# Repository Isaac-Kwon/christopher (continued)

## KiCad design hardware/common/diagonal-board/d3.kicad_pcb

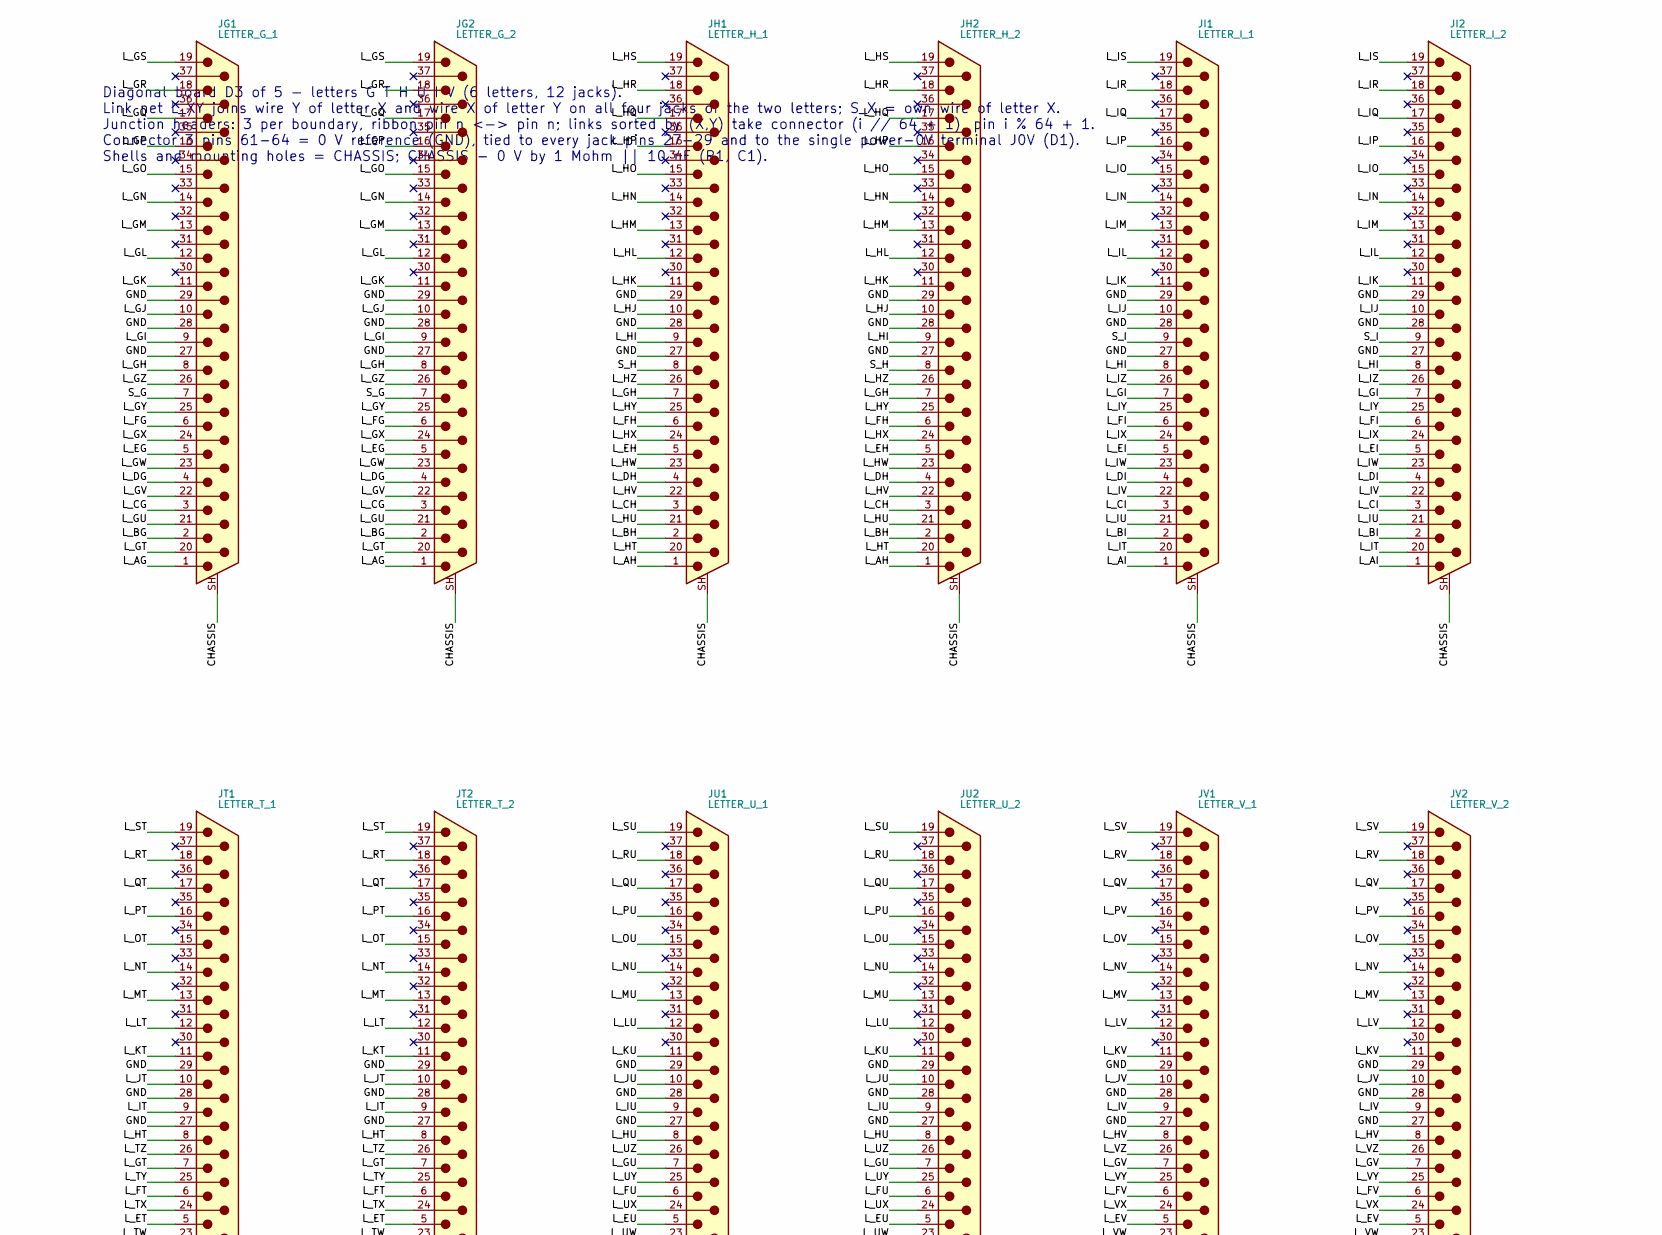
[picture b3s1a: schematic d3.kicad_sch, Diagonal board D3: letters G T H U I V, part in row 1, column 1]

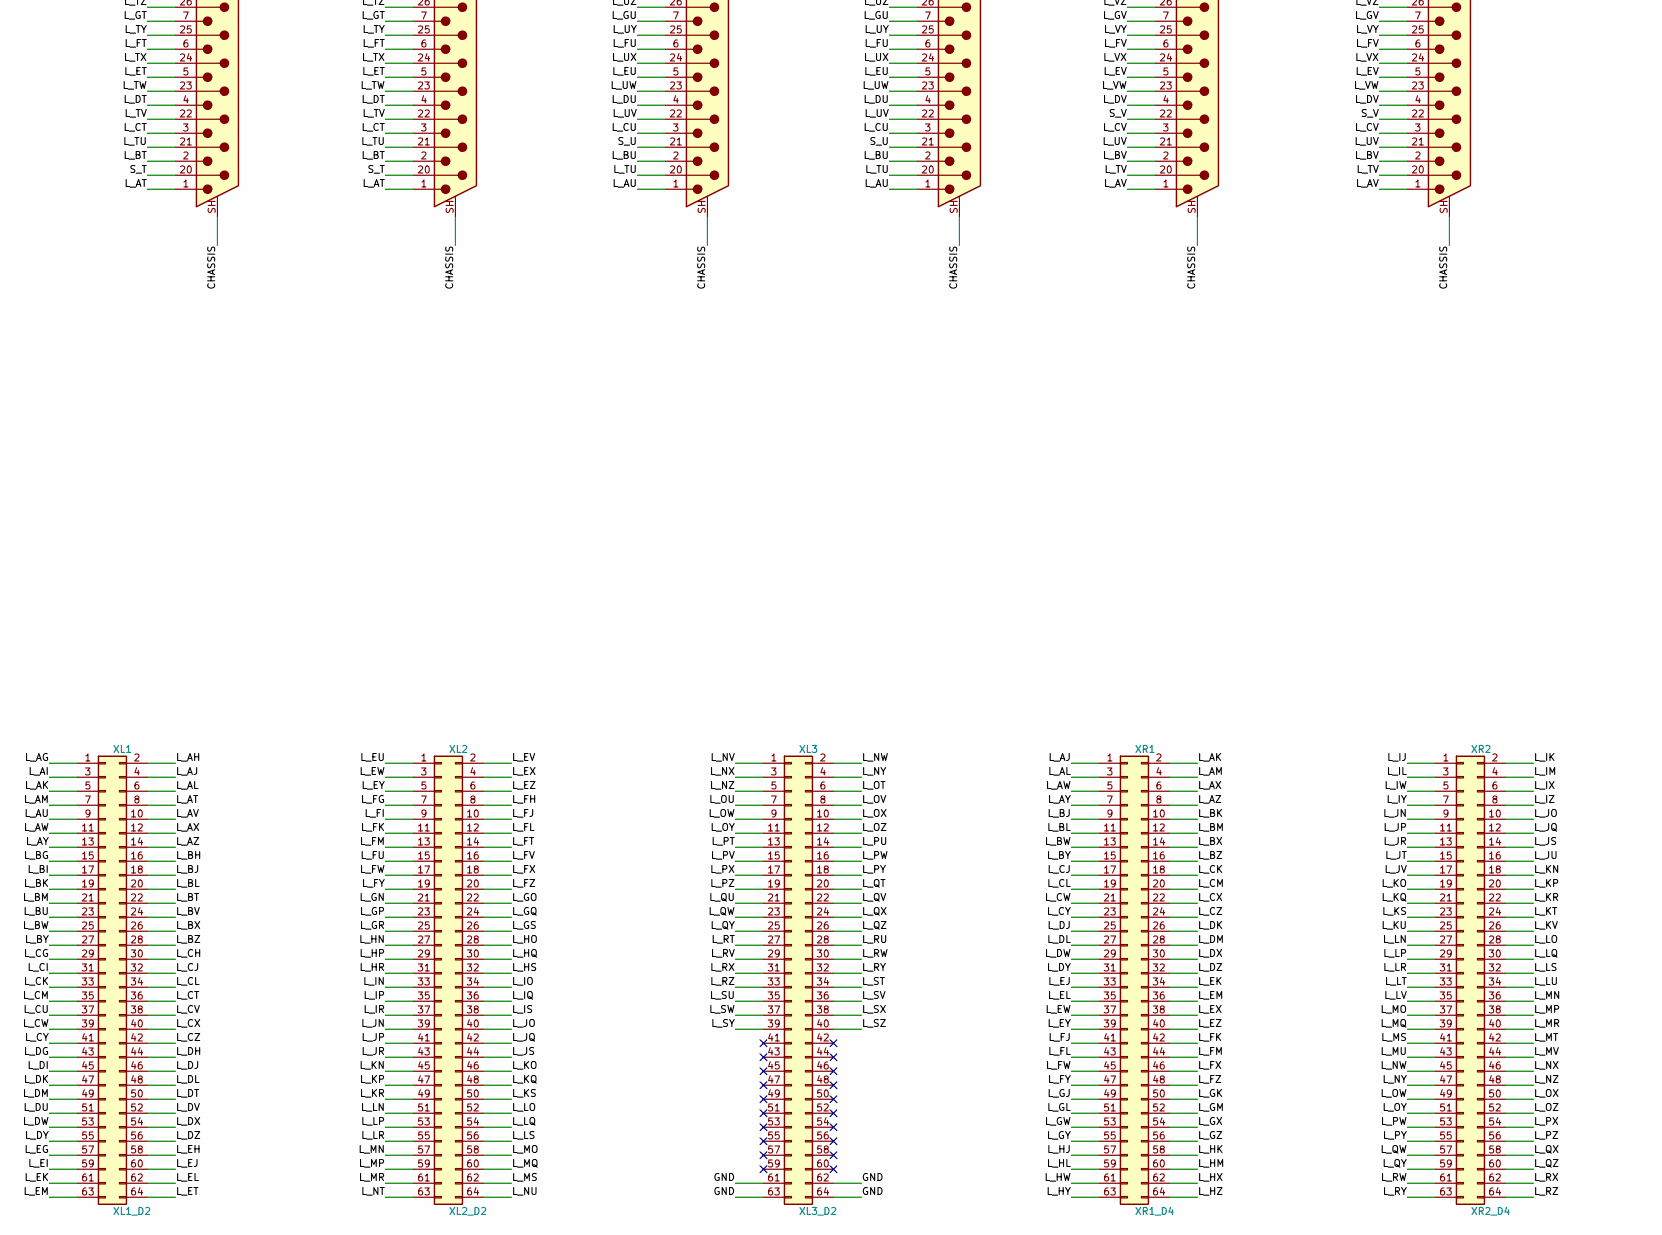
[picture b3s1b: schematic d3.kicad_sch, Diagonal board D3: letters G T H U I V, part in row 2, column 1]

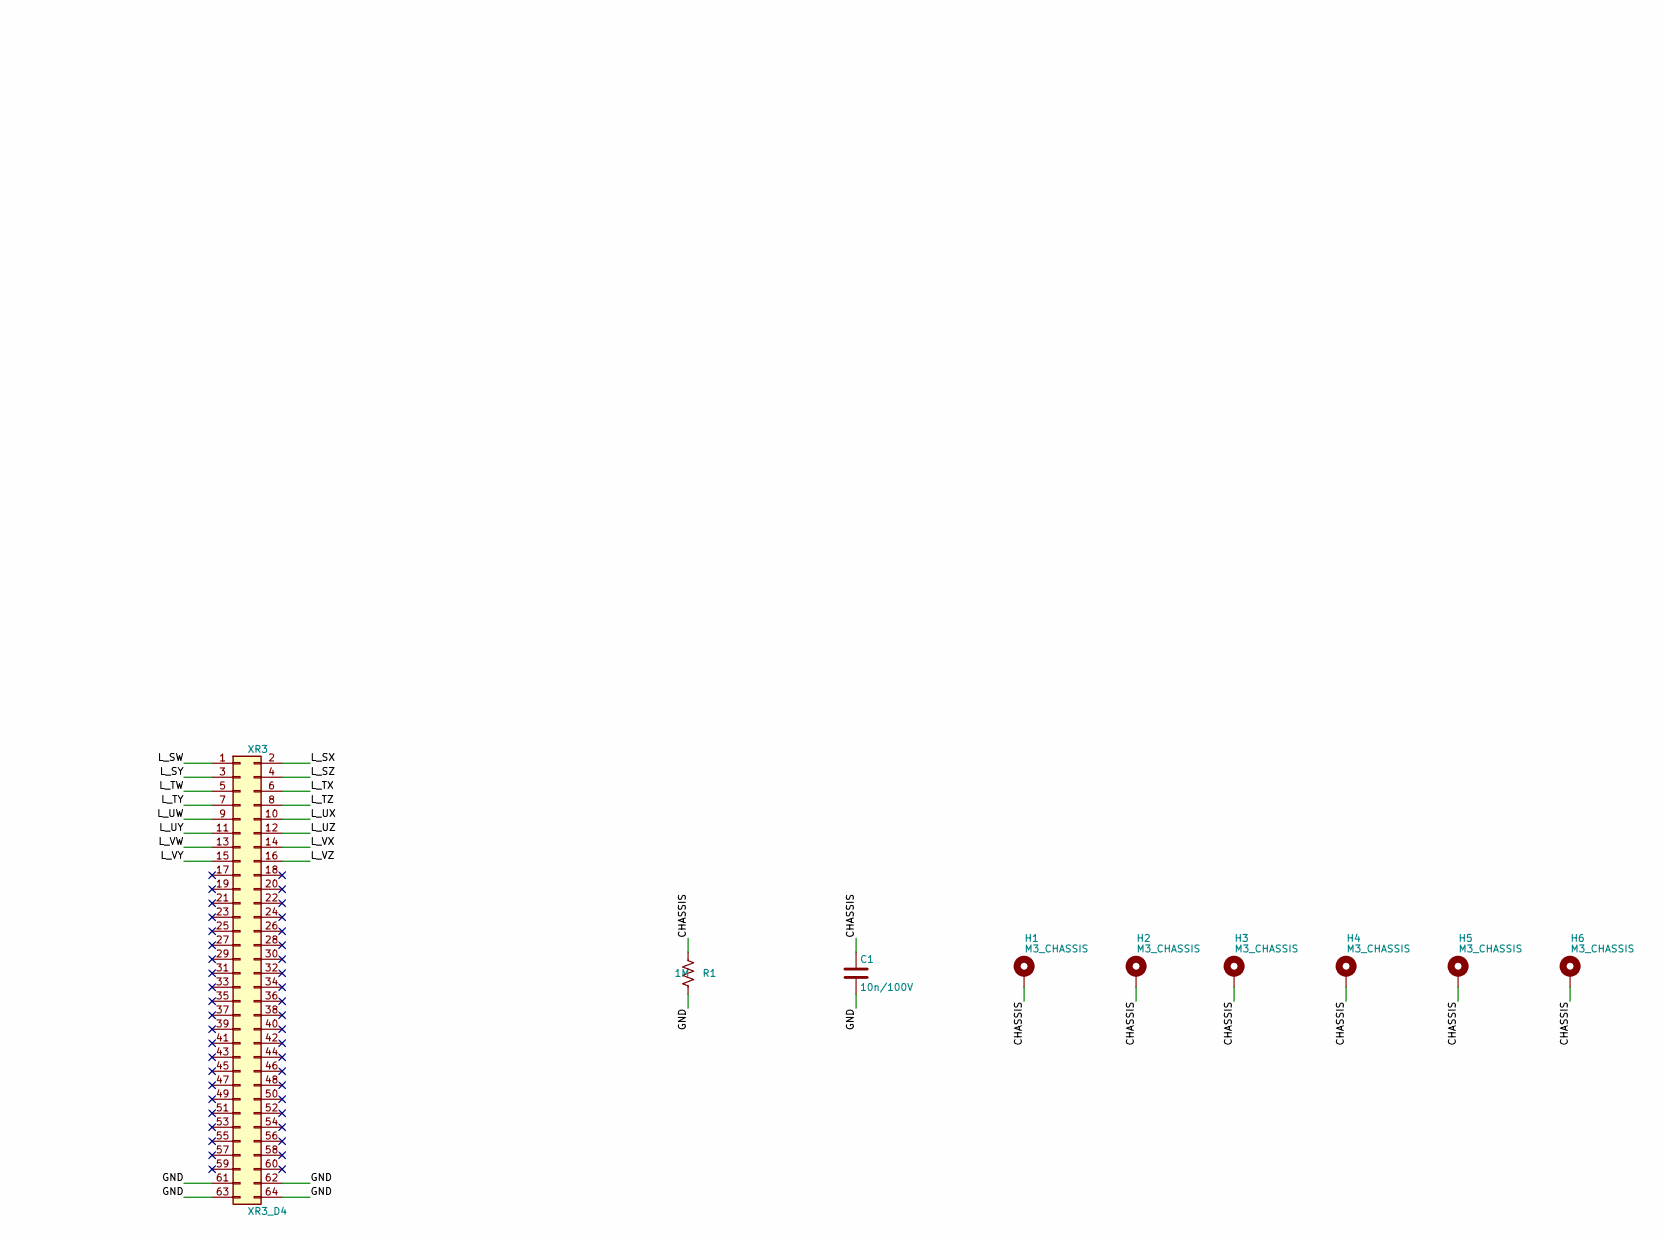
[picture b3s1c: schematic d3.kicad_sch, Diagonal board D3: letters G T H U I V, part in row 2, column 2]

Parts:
C1: 10n/100V; C_0805_2012Metric
H1, H2, H3, H4, H5, H6: M3_CHASSIS; MountingHole_3.2mm_M3_Pad
JG1: LETTER_G_1; DSUB-37_Pins_Vertical_P2.77x2.84mm_MountingHoles
JG2: LETTER_G_2; DSUB-37_Pins_Vertical_P2.77x2.84mm_MountingHoles
JH1: LETTER_H_1; DSUB-37_Pins_Vertical_P2.77x2.84mm_MountingHoles
JH2: LETTER_H_2; DSUB-37_Pins_Vertical_P2.77x2.84mm_MountingHoles
JI1: LETTER_I_1; DSUB-37_Pins_Vertical_P2.77x2.84mm_MountingHoles
JI2: LETTER_I_2; DSUB-37_Pins_Vertical_P2.77x2.84mm_MountingHoles
JT1: LETTER_T_1; DSUB-37_Pins_Vertical_P2.77x2.84mm_MountingHoles
JT2: LETTER_T_2; DSUB-37_Pins_Vertical_P2.77x2.84mm_MountingHoles
JU1: LETTER_U_1; DSUB-37_Pins_Vertical_P2.77x2.84mm_MountingHoles
JU2: LETTER_U_2; DSUB-37_Pins_Vertical_P2.77x2.84mm_MountingHoles
JV1: LETTER_V_1; DSUB-37_Pins_Vertical_P2.77x2.84mm_MountingHoles
JV2: LETTER_V_2; DSUB-37_Pins_Vertical_P2.77x2.84mm_MountingHoles
R1: 1M; R_0603_1608Metric
XL1: XL1_D2; IDC-Header_2x32_P2.54mm_Vertical
XL2: XL2_D2; IDC-Header_2x32_P2.54mm_Vertical
XL3: XL3_D2; IDC-Header_2x32_P2.54mm_Vertical
XR1: XR1_D4; IDC-Header_2x32_P2.54mm_Vertical
XR2: XR2_D4; IDC-Header_2x32_P2.54mm_Vertical
XR3: XR3_D4; IDC-Header_2x32_P2.54mm_Vertical

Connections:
/CHASSIS: C1.1, H1.1, H2.1, H3.1, H4.1, H5.1, H6.1, JG1.SH (PAD), JG2.SH (PAD), JH1.SH (PAD), JH2.SH (PAD), JI1.SH (PAD), JI2.SH (PAD), JT1.SH (PAD), JT2.SH (PAD), JU1.SH (PAD), JU2.SH (PAD), JV1.SH (PAD), JV2.SH (PAD), R1.1
/GND: C1.2, JG1.27, JG1.28, JG1.29, JG2.27, JG2.28, JG2.29, JH1.27, JH1.28, JH1.29, JH2.27, JH2.28, JH2.29, JI1.27, JI1.28, JI1.29, JI2.27, JI2.28, JI2.29, JT1.27, JT1.28, JT1.29, JT2.27, JT2.28, JT2.29, JU1.27, JU1.28, JU1.29, JU2.27, JU2.28, JU2.29, JV1.27, JV1.28, JV1.29, JV2.27, JV2.28, JV2.29, R1.2, XL3.61, XL3.62, XL3.63, XL3.64, XR3.61, XR3.62, XR3.63, XR3.64
/L_AG: JG1.1, JG2.1, XL1.1
/L_AH: JH1.1, JH2.1, XL1.2
/L_AI: JI1.1, JI2.1, XL1.3
/L_AJ: XL1.4, XR1.1
/L_AK: XL1.5, XR1.2
/L_AL: XL1.6, XR1.3
/L_AM: XL1.7, XR1.4
/L_AT: JT1.1, JT2.1, XL1.8
/L_AU: JU1.1, JU2.1, XL1.9
/L_AV: JV1.1, JV2.1, XL1.10
/L_AW: XL1.11, XR1.5
/L_AX: XL1.12, XR1.6
/L_AY: XL1.13, XR1.7
/L_AZ: XL1.14, XR1.8
/L_BG: JG1.2, JG2.2, XL1.15
/L_BH: JH1.2, JH2.2, XL1.16
/L_BI: JI1.2, JI2.2, XL1.17
/L_BJ: XL1.18, XR1.9
/L_BK: XL1.19, XR1.10
/L_BL: XL1.20, XR1.11
/L_BM: XL1.21, XR1.12
/L_BT: JT1.2, JT2.2, XL1.22
/L_BU: JU1.2, JU2.2, XL1.23
/L_BV: JV1.2, JV2.2, XL1.24
/L_BW: XL1.25, XR1.13
/L_BX: XL1.26, XR1.14
/L_BY: XL1.27, XR1.15
/L_BZ: XL1.28, XR1.16
/L_CG: JG1.3, JG2.3, XL1.29
/L_CH: JH1.3, JH2.3, XL1.30
/L_CI: JI1.3, JI2.3, XL1.31
/L_CJ: XL1.32, XR1.17
/L_CK: XL1.33, XR1.18
/L_CL: XL1.34, XR1.19
/L_CM: XL1.35, XR1.20
/L_CT: JT1.3, JT2.3, XL1.36
/L_CU: JU1.3, JU2.3, XL1.37
/L_CV: JV1.3, JV2.3, XL1.38
/L_CW: XL1.39, XR1.21
/L_CX: XL1.40, XR1.22
/L_CY: XL1.41, XR1.23
/L_CZ: XL1.42, XR1.24
/L_DG: JG1.4, JG2.4, XL1.43
/L_DH: JH1.4, JH2.4, XL1.44
/L_DI: JI1.4, JI2.4, XL1.45
/L_DJ: XL1.46, XR1.25
/L_DK: XL1.47, XR1.26
/L_DL: XL1.48, XR1.27
/L_DM: XL1.49, XR1.28
/L_DT: JT1.4, JT2.4, XL1.50
/L_DU: JU1.4, JU2.4, XL1.51
/L_DV: JV1.4, JV2.4, XL1.52
/L_DW: XL1.53, XR1.29
/L_DX: XL1.54, XR1.30
/L_DY: XL1.55, XR1.31
/L_DZ: XL1.56, XR1.32
/L_EG: JG1.5, JG2.5, XL1.57
/L_EH: JH1.5, JH2.5, XL1.58
/L_EI: JI1.5, JI2.5, XL1.59
/L_EJ: XL1.60, XR1.33
/L_EK: XL1.61, XR1.34
/L_EL: XL1.62, XR1.35
/L_EM: XL1.63, XR1.36
/L_ET: JT1.5, JT2.5, XL1.64
/L_EU: JU1.5, JU2.5, XL2.1
/L_EV: JV1.5, JV2.5, XL2.2
/L_EW: XL2.3, XR1.37
/L_EX: XL2.4, XR1.38
/L_EY: XL2.5, XR1.39
/L_EZ: XL2.6, XR1.40
/L_FG: JG1.6, JG2.6, XL2.7
/L_FH: JH1.6, JH2.6, XL2.8
/L_FI: JI1.6, JI2.6, XL2.9
/L_FJ: XL2.10, XR1.41
/L_FK: XL2.11, XR1.42
/L_FL: XL2.12, XR1.43
/L_FM: XL2.13, XR1.44
/L_FT: JT1.6, JT2.6, XL2.14
/L_FU: JU1.6, JU2.6, XL2.15
/L_FV: JV1.6, JV2.6, XL2.16
/L_FW: XL2.17, XR1.45
/L_FX: XL2.18, XR1.46
/L_FY: XL2.19, XR1.47
/L_FZ: XL2.20, XR1.48
/L_GH: JG1.8, JG2.8, JH1.7, JH2.7
/L_GI: JG1.9, JG2.9, JI1.7, JI2.7
/L_GJ: JG1.10, JG2.10, XR1.49
/L_GK: JG1.11, JG2.11, XR1.50
/L_GL: JG1.12, JG2.12, XR1.51
/L_GM: JG1.13, JG2.13, XR1.52
/L_GN: JG1.14, JG2.14, XL2.21
/L_GO: JG1.15, JG2.15, XL2.22
/L_GP: JG1.16, JG2.16, XL2.23
/L_GQ: JG1.17, JG2.17, XL2.24
/L_GR: JG1.18, JG2.18, XL2.25
/L_GS: JG1.19, JG2.19, XL2.26
/L_GT: JG1.20, JG2.20, JT1.7, JT2.7
/L_GU: JG1.21, JG2.21, JU1.7, JU2.7
/L_GV: JG1.22, JG2.22, JV1.7, JV2.7
/L_GW: JG1.23, JG2.23, XR1.53
/L_GX: JG1.24, JG2.24, XR1.54
/L_GY: JG1.25, JG2.25, XR1.55
/L_GZ: JG1.26, JG2.26, XR1.56
/L_HI: JH1.9, JH2.9, JI1.8, JI2.8
/L_HJ: JH1.10, JH2.10, XR1.57
/L_HK: JH1.11, JH2.11, XR1.58
/L_HL: JH1.12, JH2.12, XR1.59
/L_HM: JH1.13, JH2.13, XR1.60
/L_HN: JH1.14, JH2.14, XL2.27
/L_HO: JH1.15, JH2.15, XL2.28
/L_HP: JH1.16, JH2.16, XL2.29
/L_HQ: JH1.17, JH2.17, XL2.30
/L_HR: JH1.18, JH2.18, XL2.31
/L_HS: JH1.19, JH2.19, XL2.32
/L_HT: JH1.20, JH2.20, JT1.8, JT2.8
/L_HU: JH1.21, JH2.21, JU1.8, JU2.8
/L_HV: JH1.22, JH2.22, JV1.8, JV2.8
/L_HW: JH1.23, JH2.23, XR1.61
/L_HX: JH1.24, JH2.24, XR1.62
/L_HY: JH1.25, JH2.25, XR1.63
/L_HZ: JH1.26, JH2.26, XR1.64
/L_IJ: JI1.10, JI2.10, XR2.1
/L_IK: JI1.11, JI2.11, XR2.2
/L_IL: JI1.12, JI2.12, XR2.3
/L_IM: JI1.13, JI2.13, XR2.4
/L_IN: JI1.14, JI2.14, XL2.33
/L_IO: JI1.15, JI2.15, XL2.34
/L_IP: JI1.16, JI2.16, XL2.35
/L_IQ: JI1.17, JI2.17, XL2.36
/L_IR: JI1.18, JI2.18, XL2.37
/L_IS: JI1.19, JI2.19, XL2.38
/L_IT: JI1.20, JI2.20, JT1.9, JT2.9
/L_IU: JI1.21, JI2.21, JU1.9, JU2.9
/L_IV: JI1.22, JI2.22, JV1.9, JV2.9
/L_IW: JI1.23, JI2.23, XR2.5
/L_IX: JI1.24, JI2.24, XR2.6
/L_IY: JI1.25, JI2.25, XR2.7
/L_IZ: JI1.26, JI2.26, XR2.8
/L_JN: XL2.39, XR2.9
/L_JO: XL2.40, XR2.10
/L_JP: XL2.41, XR2.11
/L_JQ: XL2.42, XR2.12
/L_JR: XL2.43, XR2.13
/L_JS: XL2.44, XR2.14
/L_JT: JT1.10, JT2.10, XR2.15
/L_JU: JU1.10, JU2.10, XR2.16
/L_JV: JV1.10, JV2.10, XR2.17
/L_KN: XL2.45, XR2.18
/L_KO: XL2.46, XR2.19
/L_KP: XL2.47, XR2.20
/L_KQ: XL2.48, XR2.21
/L_KR: XL2.49, XR2.22
/L_KS: XL2.50, XR2.23
/L_KT: JT1.11, JT2.11, XR2.24
/L_KU: JU1.11, JU2.11, XR2.25
/L_KV: JV1.11, JV2.11, XR2.26
/L_LN: XL2.51, XR2.27
/L_LO: XL2.52, XR2.28
/L_LP: XL2.53, XR2.29
/L_LQ: XL2.54, XR2.30
/L_LR: XL2.55, XR2.31
/L_LS: XL2.56, XR2.32
/L_LT: JT1.12, JT2.12, XR2.33
/L_LU: JU1.12, JU2.12, XR2.34
/L_LV: JV1.12, JV2.12, XR2.35
/L_MN: XL2.57, XR2.36
/L_MO: XL2.58, XR2.37
/L_MP: XL2.59, XR2.38
/L_MQ: XL2.60, XR2.39
/L_MR: XL2.61, XR2.40
/L_MS: XL2.62, XR2.41
/L_MT: JT1.13, JT2.13, XR2.42
/L_MU: JU1.13, JU2.13, XR2.43
/L_MV: JV1.13, JV2.13, XR2.44
/L_NT: JT1.14, JT2.14, XL2.63
/L_NU: JU1.14, JU2.14, XL2.64
/L_NV: JV1.14, JV2.14, XL3.1
/L_NW: XL3.2, XR2.45
/L_NX: XL3.3, XR2.46
/L_NY: XL3.4, XR2.47
/L_NZ: XL3.5, XR2.48
/L_OT: JT1.15, JT2.15, XL3.6
/L_OU: JU1.15, JU2.15, XL3.7
/L_OV: JV1.15, JV2.15, XL3.8
/L_OW: XL3.9, XR2.49
/L_OX: XL3.10, XR2.50
/L_OY: XL3.11, XR2.51
/L_OZ: XL3.12, XR2.52
/L_PT: JT1.16, JT2.16, XL3.13
/L_PU: JU1.16, JU2.16, XL3.14
/L_PV: JV1.16, JV2.16, XL3.15
/L_PW: XL3.16, XR2.53
/L_PX: XL3.17, XR2.54
/L_PY: XL3.18, XR2.55
/L_PZ: XL3.19, XR2.56
/L_QT: JT1.17, JT2.17, XL3.20
/L_QU: JU1.17, JU2.17, XL3.21
/L_QV: JV1.17, JV2.17, XL3.22
/L_QW: XL3.23, XR2.57
/L_QX: XL3.24, XR2.58
/L_QY: XL3.25, XR2.59
/L_QZ: XL3.26, XR2.60
/L_RT: JT1.18, JT2.18, XL3.27
/L_RU: JU1.18, JU2.18, XL3.28
/L_RV: JV1.18, JV2.18, XL3.29
/L_RW: XL3.30, XR2.61
/L_RX: XL3.31, XR2.62
/L_RY: XL3.32, XR2.63
/L_RZ: XL3.33, XR2.64
/L_ST: JT1.19, JT2.19, XL3.34
/L_SU: JU1.19, JU2.19, XL3.35
/L_SV: JV1.19, JV2.19, XL3.36
/L_SW: XL3.37, XR3.1
/L_SX: XL3.38, XR3.2
/L_SY: XL3.39, XR3.3
/L_SZ: XL3.40, XR3.4
/L_TU: JT1.21, JT2.21, JU1.20, JU2.20
/L_TV: JT1.22, JT2.22, JV1.20, JV2.20
/L_TW: JT1.23, JT2.23, XR3.5
/L_TX: JT1.24, JT2.24, XR3.6
/L_TY: JT1.25, JT2.25, XR3.7
/L_TZ: JT1.26, JT2.26, XR3.8
/L_UV: JU1.22, JU2.22, JV1.21, JV2.21
/L_UW: JU1.23, JU2.23, XR3.9
/L_UX: JU1.24, JU2.24, XR3.10
/L_UY: JU1.25, JU2.25, XR3.11
/L_UZ: JU1.26, JU2.26, XR3.12
/L_VW: JV1.23, JV2.23, XR3.13
/L_VX: JV1.24, JV2.24, XR3.14
/L_VY: JV1.25, JV2.25, XR3.15
/L_VZ: JV1.26, JV2.26, XR3.16
/S_G: JG1.7, JG2.7
/S_H: JH1.8, JH2.8
/S_I: JI1.9, JI2.9
/S_T: JT1.20, JT2.20
/S_U: JU1.21, JU2.21
/S_V: JV1.22, JV2.22

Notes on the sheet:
Diagonal board D3 of 5 - letters G T H U I V (6 letters, 12 jacks). Link net L_XY joins wire Y of letter X and wire X of letter Y on all four jacks of the two letters; S_X = own wire of letter X. Junction headers: 3 per boundary, ribbon pin n <-> pin n; links sorted by (X,Y) take connector (i // 64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

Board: 4 copper layers, 26 parts (6 on the bottom side), 239 nets, no tracks yet.

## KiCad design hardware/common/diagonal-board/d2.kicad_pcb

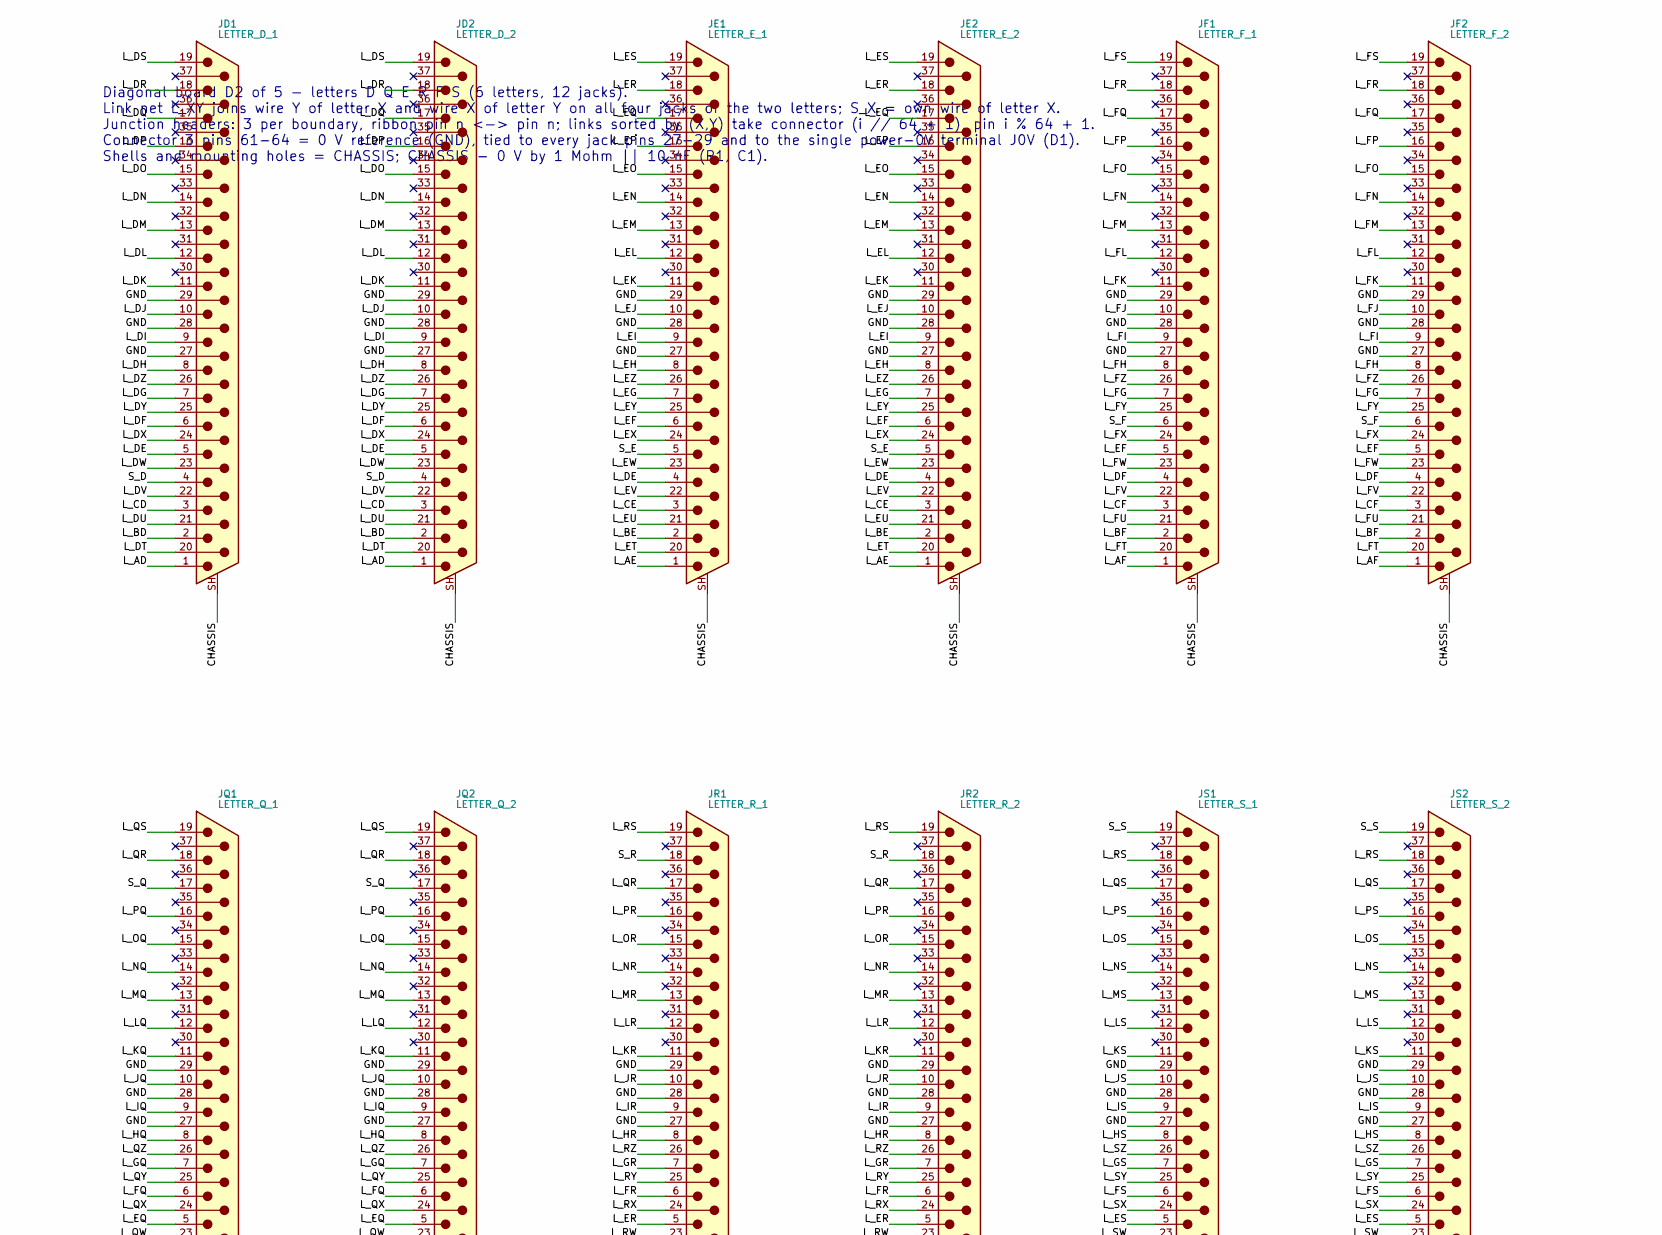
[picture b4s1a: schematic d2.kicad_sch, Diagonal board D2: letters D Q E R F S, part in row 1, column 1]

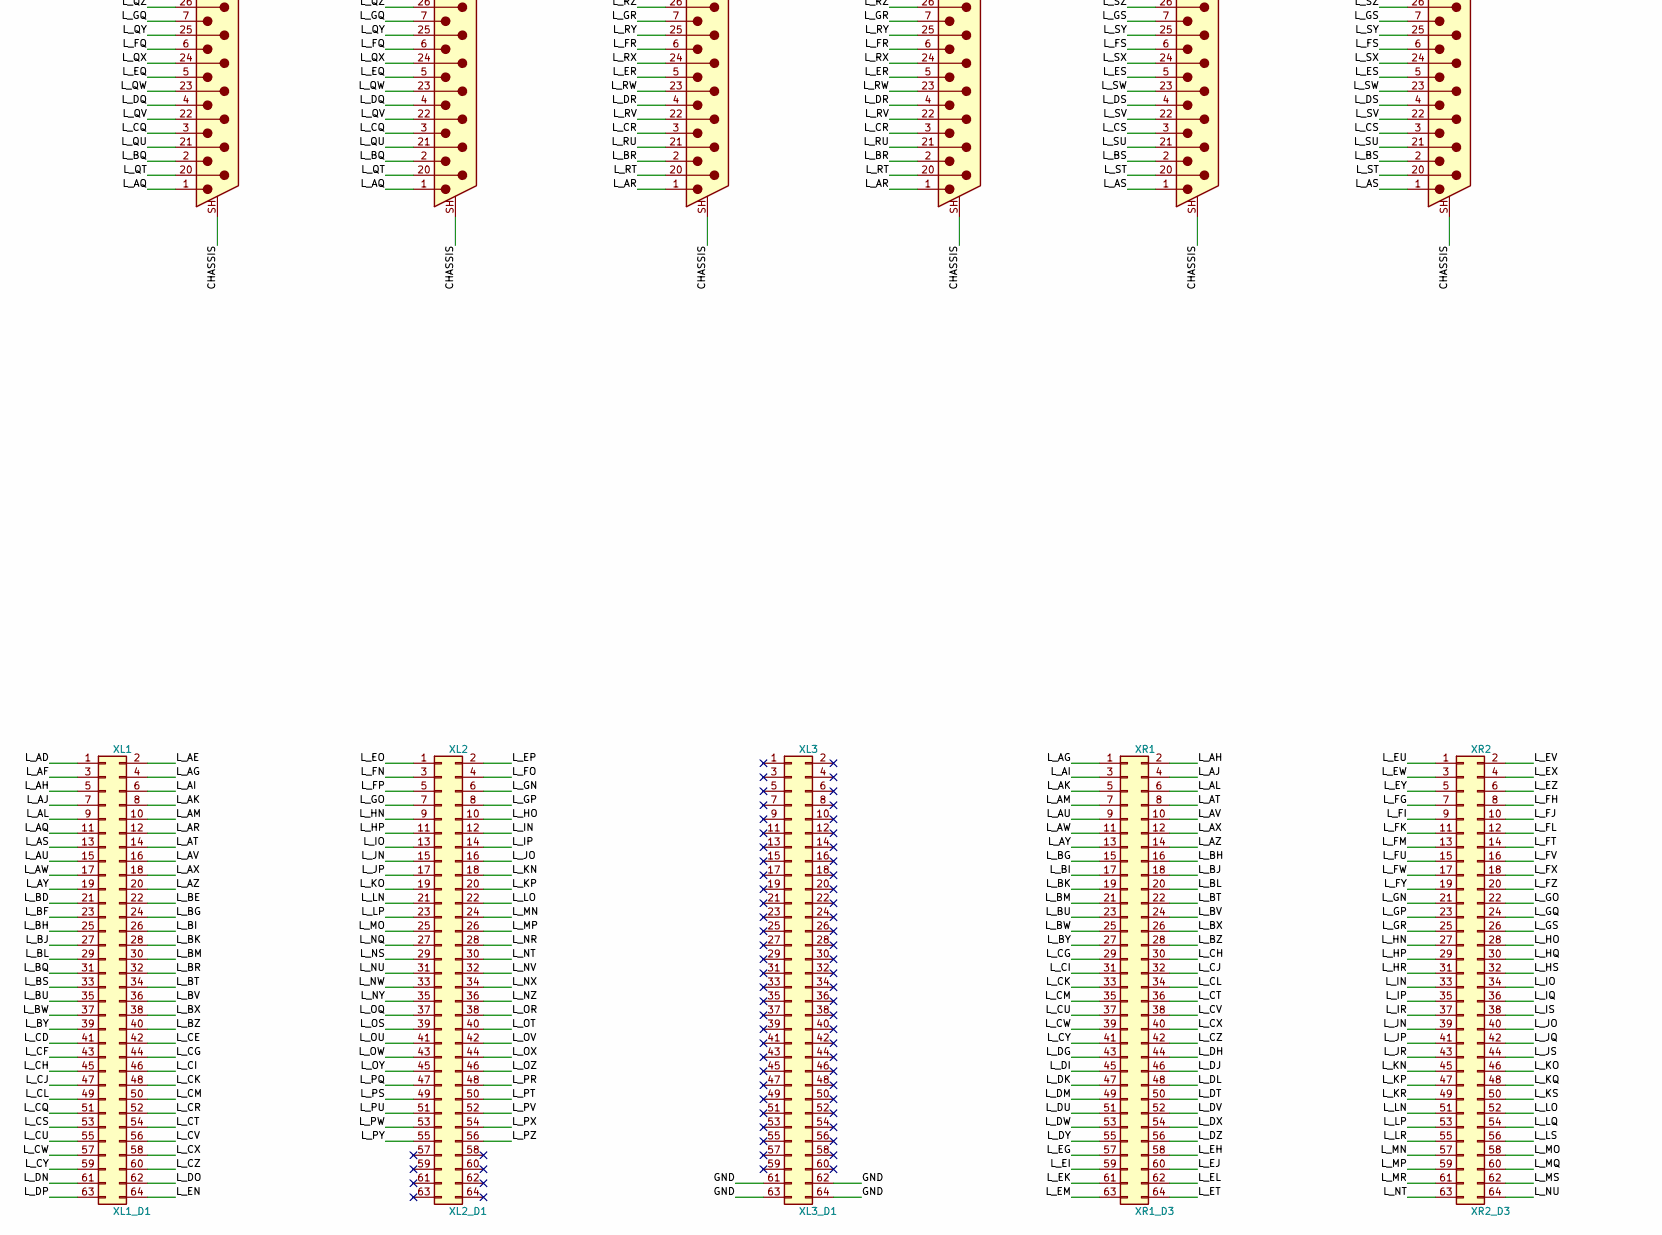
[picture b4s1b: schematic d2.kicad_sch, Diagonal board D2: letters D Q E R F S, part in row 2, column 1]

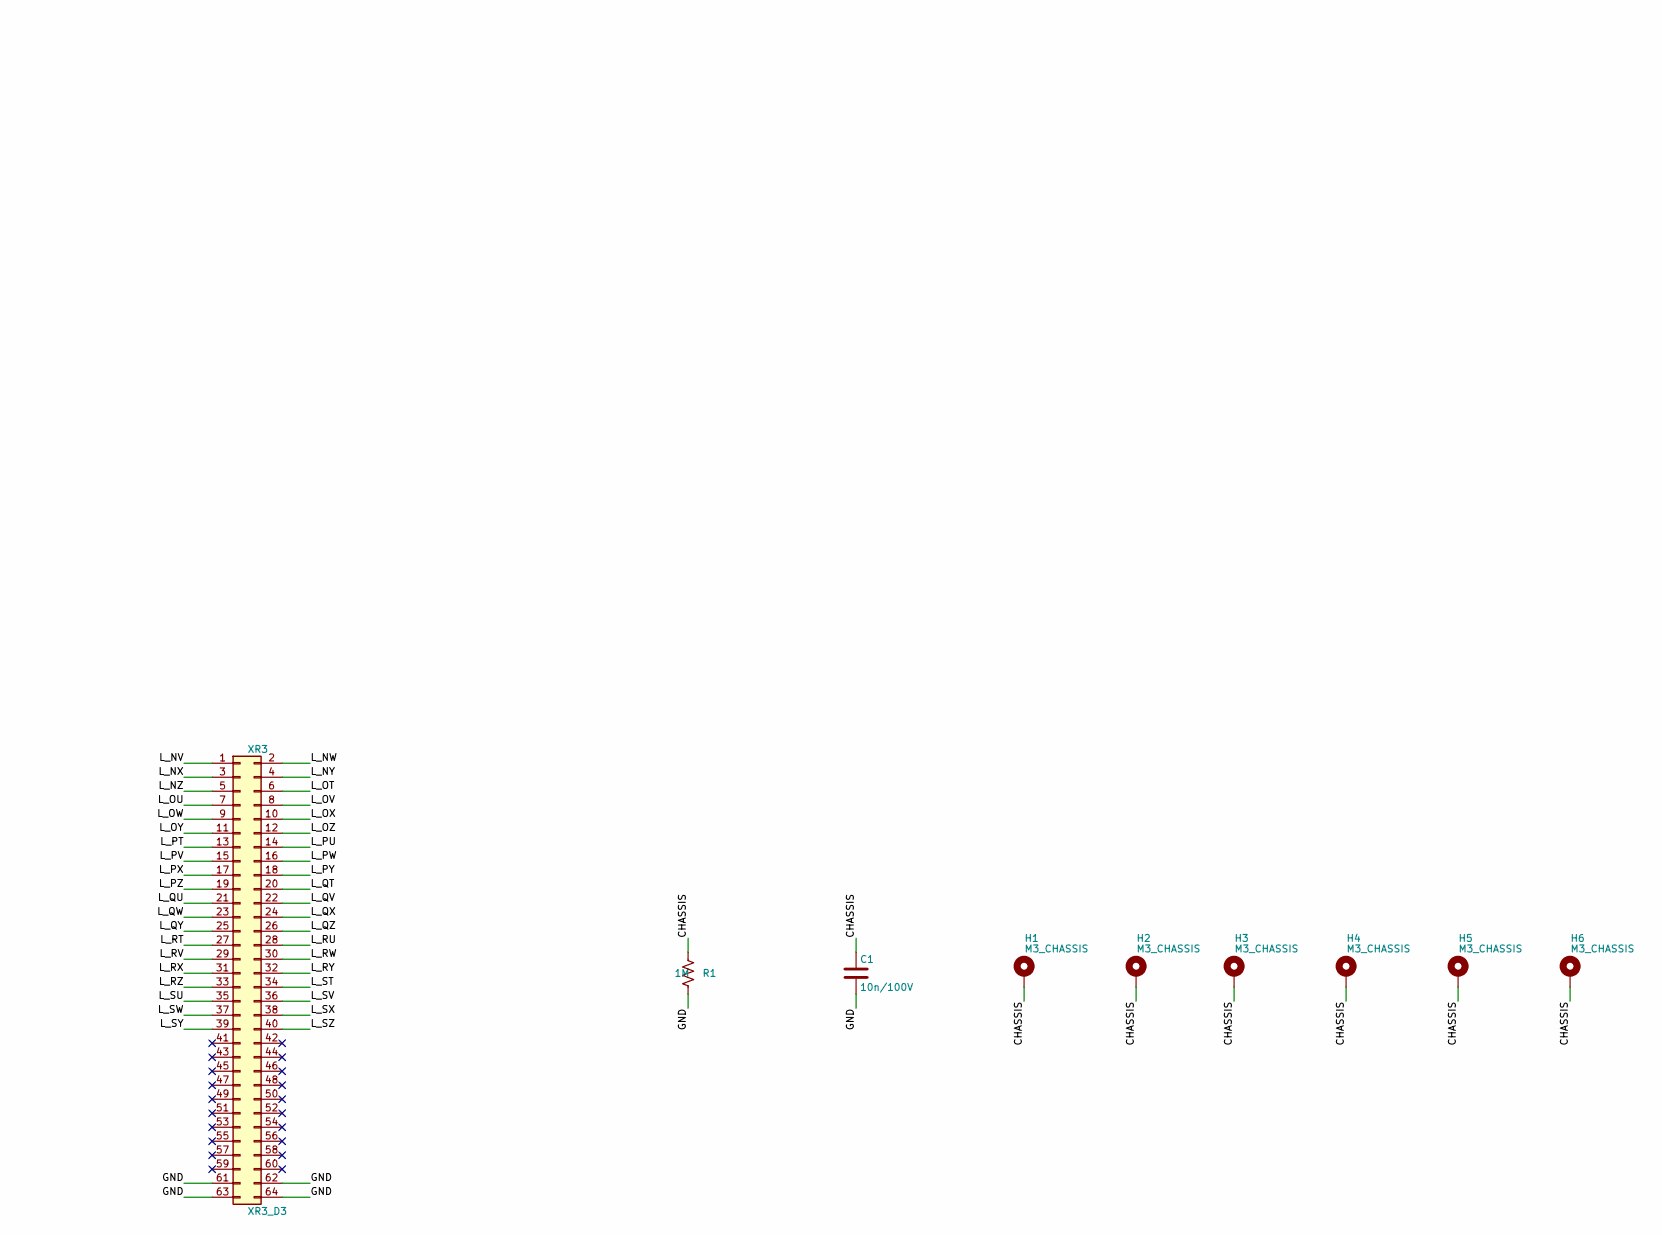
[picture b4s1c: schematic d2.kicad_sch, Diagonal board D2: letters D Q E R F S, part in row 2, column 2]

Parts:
C1: 10n/100V; C_0805_2012Metric
H1, H2, H3, H4, H5, H6: M3_CHASSIS; MountingHole_3.2mm_M3_Pad
JD1: LETTER_D_1; DSUB-37_Pins_Vertical_P2.77x2.84mm_MountingHoles
JD2: LETTER_D_2; DSUB-37_Pins_Vertical_P2.77x2.84mm_MountingHoles
JE1: LETTER_E_1; DSUB-37_Pins_Vertical_P2.77x2.84mm_MountingHoles
JE2: LETTER_E_2; DSUB-37_Pins_Vertical_P2.77x2.84mm_MountingHoles
JF1: LETTER_F_1; DSUB-37_Pins_Vertical_P2.77x2.84mm_MountingHoles
JF2: LETTER_F_2; DSUB-37_Pins_Vertical_P2.77x2.84mm_MountingHoles
JQ1: LETTER_Q_1; DSUB-37_Pins_Vertical_P2.77x2.84mm_MountingHoles
JQ2: LETTER_Q_2; DSUB-37_Pins_Vertical_P2.77x2.84mm_MountingHoles
JR1: LETTER_R_1; DSUB-37_Pins_Vertical_P2.77x2.84mm_MountingHoles
JR2: LETTER_R_2; DSUB-37_Pins_Vertical_P2.77x2.84mm_MountingHoles
JS1: LETTER_S_1; DSUB-37_Pins_Vertical_P2.77x2.84mm_MountingHoles
JS2: LETTER_S_2; DSUB-37_Pins_Vertical_P2.77x2.84mm_MountingHoles
R1: 1M; R_0603_1608Metric
XL1: XL1_D1; IDC-Header_2x32_P2.54mm_Vertical
XL2: XL2_D1; IDC-Header_2x32_P2.54mm_Vertical
XL3: XL3_D1; IDC-Header_2x32_P2.54mm_Vertical
XR1: XR1_D3; IDC-Header_2x32_P2.54mm_Vertical
XR2: XR2_D3; IDC-Header_2x32_P2.54mm_Vertical
XR3: XR3_D3; IDC-Header_2x32_P2.54mm_Vertical

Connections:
/CHASSIS: C1.1, H1.1, H2.1, H3.1, H4.1, H5.1, H6.1, JD1.SH (PAD), JD2.SH (PAD), JE1.SH (PAD), JE2.SH (PAD), JF1.SH (PAD), JF2.SH (PAD), JQ1.SH (PAD), JQ2.SH (PAD), JR1.SH (PAD), JR2.SH (PAD), JS1.SH (PAD), JS2.SH (PAD), R1.1
/GND: C1.2, JD1.27, JD1.28, JD1.29, JD2.27, JD2.28, JD2.29, JE1.27, JE1.28, JE1.29, JE2.27, JE2.28, JE2.29, JF1.27, JF1.28, JF1.29, JF2.27, JF2.28, JF2.29, JQ1.27, JQ1.28, JQ1.29, JQ2.27, JQ2.28, JQ2.29, JR1.27, JR1.28, JR1.29, JR2.27, JR2.28, JR2.29, JS1.27, JS1.28, JS1.29, JS2.27, JS2.28, JS2.29, R1.2, XL3.61, XL3.62, XL3.63, XL3.64, XR3.61, XR3.62, XR3.63, XR3.64
/L_AD: JD1.1, JD2.1, XL1.1
/L_AE: JE1.1, JE2.1, XL1.2
/L_AF: JF1.1, JF2.1, XL1.3
/L_AG: XL1.4, XR1.1
/L_AH: XL1.5, XR1.2
/L_AI: XL1.6, XR1.3
/L_AJ: XL1.7, XR1.4
/L_AK: XL1.8, XR1.5
/L_AL: XL1.9, XR1.6
/L_AM: XL1.10, XR1.7
/L_AQ: JQ1.1, JQ2.1, XL1.11
/L_AR: JR1.1, JR2.1, XL1.12
/L_AS: JS1.1, JS2.1, XL1.13
/L_AT: XL1.14, XR1.8
/L_AU: XL1.15, XR1.9
/L_AV: XL1.16, XR1.10
/L_AW: XL1.17, XR1.11
/L_AX: XL1.18, XR1.12
/L_AY: XL1.19, XR1.13
/L_AZ: XL1.20, XR1.14
/L_BD: JD1.2, JD2.2, XL1.21
/L_BE: JE1.2, JE2.2, XL1.22
/L_BF: JF1.2, JF2.2, XL1.23
/L_BG: XL1.24, XR1.15
/L_BH: XL1.25, XR1.16
/L_BI: XL1.26, XR1.17
/L_BJ: XL1.27, XR1.18
/L_BK: XL1.28, XR1.19
/L_BL: XL1.29, XR1.20
/L_BM: XL1.30, XR1.21
/L_BQ: JQ1.2, JQ2.2, XL1.31
/L_BR: JR1.2, JR2.2, XL1.32
/L_BS: JS1.2, JS2.2, XL1.33
/L_BT: XL1.34, XR1.22
/L_BU: XL1.35, XR1.23
/L_BV: XL1.36, XR1.24
/L_BW: XL1.37, XR1.25
/L_BX: XL1.38, XR1.26
/L_BY: XL1.39, XR1.27
/L_BZ: XL1.40, XR1.28
/L_CD: JD1.3, JD2.3, XL1.41
/L_CE: JE1.3, JE2.3, XL1.42
/L_CF: JF1.3, JF2.3, XL1.43
/L_CG: XL1.44, XR1.29
/L_CH: XL1.45, XR1.30
/L_CI: XL1.46, XR1.31
/L_CJ: XL1.47, XR1.32
/L_CK: XL1.48, XR1.33
/L_CL: XL1.49, XR1.34
/L_CM: XL1.50, XR1.35
/L_CQ: JQ1.3, JQ2.3, XL1.51
/L_CR: JR1.3, JR2.3, XL1.52
/L_CS: JS1.3, JS2.3, XL1.53
/L_CT: XL1.54, XR1.36
/L_CU: XL1.55, XR1.37
/L_CV: XL1.56, XR1.38
/L_CW: XL1.57, XR1.39
/L_CX: XL1.58, XR1.40
/L_CY: XL1.59, XR1.41
/L_CZ: XL1.60, XR1.42
/L_DE: JD1.5, JD2.5, JE1.4, JE2.4
/L_DF: JD1.6, JD2.6, JF1.4, JF2.4
/L_DG: JD1.7, JD2.7, XR1.43
/L_DH: JD1.8, JD2.8, XR1.44
/L_DI: JD1.9, JD2.9, XR1.45
/L_DJ: JD1.10, JD2.10, XR1.46
/L_DK: JD1.11, JD2.11, XR1.47
/L_DL: JD1.12, JD2.12, XR1.48
/L_DM: JD1.13, JD2.13, XR1.49
/L_DN: JD1.14, JD2.14, XL1.61
/L_DO: JD1.15, JD2.15, XL1.62
/L_DP: JD1.16, JD2.16, XL1.63
/L_DQ: JD1.17, JD2.17, JQ1.4, JQ2.4
/L_DR: JD1.18, JD2.18, JR1.4, JR2.4
/L_DS: JD1.19, JD2.19, JS1.4, JS2.4
/L_DT: JD1.20, JD2.20, XR1.50
/L_DU: JD1.21, JD2.21, XR1.51
/L_DV: JD1.22, JD2.22, XR1.52
/L_DW: JD1.23, JD2.23, XR1.53
/L_DX: JD1.24, JD2.24, XR1.54
/L_DY: JD1.25, JD2.25, XR1.55
/L_DZ: JD1.26, JD2.26, XR1.56
/L_EF: JE1.6, JE2.6, JF1.5, JF2.5
/L_EG: JE1.7, JE2.7, XR1.57
/L_EH: JE1.8, JE2.8, XR1.58
/L_EI: JE1.9, JE2.9, XR1.59
/L_EJ: JE1.10, JE2.10, XR1.60
/L_EK: JE1.11, JE2.11, XR1.61
/L_EL: JE1.12, JE2.12, XR1.62
/L_EM: JE1.13, JE2.13, XR1.63
/L_EN: JE1.14, JE2.14, XL1.64
/L_EO: JE1.15, JE2.15, XL2.1
/L_EP: JE1.16, JE2.16, XL2.2
/L_EQ: JE1.17, JE2.17, JQ1.5, JQ2.5
/L_ER: JE1.18, JE2.18, JR1.5, JR2.5
/L_ES: JE1.19, JE2.19, JS1.5, JS2.5
/L_ET: JE1.20, JE2.20, XR1.64
/L_EU: JE1.21, JE2.21, XR2.1
/L_EV: JE1.22, JE2.22, XR2.2
/L_EW: JE1.23, JE2.23, XR2.3
/L_EX: JE1.24, JE2.24, XR2.4
/L_EY: JE1.25, JE2.25, XR2.5
/L_EZ: JE1.26, JE2.26, XR2.6
/L_FG: JF1.7, JF2.7, XR2.7
/L_FH: JF1.8, JF2.8, XR2.8
/L_FI: JF1.9, JF2.9, XR2.9
/L_FJ: JF1.10, JF2.10, XR2.10
/L_FK: JF1.11, JF2.11, XR2.11
/L_FL: JF1.12, JF2.12, XR2.12
/L_FM: JF1.13, JF2.13, XR2.13
/L_FN: JF1.14, JF2.14, XL2.3
/L_FO: JF1.15, JF2.15, XL2.4
/L_FP: JF1.16, JF2.16, XL2.5
/L_FQ: JF1.17, JF2.17, JQ1.6, JQ2.6
/L_FR: JF1.18, JF2.18, JR1.6, JR2.6
/L_FS: JF1.19, JF2.19, JS1.6, JS2.6
/L_FT: JF1.20, JF2.20, XR2.14
/L_FU: JF1.21, JF2.21, XR2.15
/L_FV: JF1.22, JF2.22, XR2.16
/L_FW: JF1.23, JF2.23, XR2.17
/L_FX: JF1.24, JF2.24, XR2.18
/L_FY: JF1.25, JF2.25, XR2.19
/L_FZ: JF1.26, JF2.26, XR2.20
/L_GN: XL2.6, XR2.21
/L_GO: XL2.7, XR2.22
/L_GP: XL2.8, XR2.23
/L_GQ: JQ1.7, JQ2.7, XR2.24
/L_GR: JR1.7, JR2.7, XR2.25
/L_GS: JS1.7, JS2.7, XR2.26
/L_HN: XL2.9, XR2.27
/L_HO: XL2.10, XR2.28
/L_HP: XL2.11, XR2.29
/L_HQ: JQ1.8, JQ2.8, XR2.30
/L_HR: JR1.8, JR2.8, XR2.31
/L_HS: JS1.8, JS2.8, XR2.32
/L_IN: XL2.12, XR2.33
/L_IO: XL2.13, XR2.34
/L_IP: XL2.14, XR2.35
/L_IQ: JQ1.9, JQ2.9, XR2.36
/L_IR: JR1.9, JR2.9, XR2.37
/L_IS: JS1.9, JS2.9, XR2.38
/L_JN: XL2.15, XR2.39
/L_JO: XL2.16, XR2.40
/L_JP: XL2.17, XR2.41
/L_JQ: JQ1.10, JQ2.10, XR2.42
/L_JR: JR1.10, JR2.10, XR2.43
/L_JS: JS1.10, JS2.10, XR2.44
/L_KN: XL2.18, XR2.45
/L_KO: XL2.19, XR2.46
/L_KP: XL2.20, XR2.47
/L_KQ: JQ1.11, JQ2.11, XR2.48
/L_KR: JR1.11, JR2.11, XR2.49
/L_KS: JS1.11, JS2.11, XR2.50
/L_LN: XL2.21, XR2.51
/L_LO: XL2.22, XR2.52
/L_LP: XL2.23, XR2.53
/L_LQ: JQ1.12, JQ2.12, XR2.54
/L_LR: JR1.12, JR2.12, XR2.55
/L_LS: JS1.12, JS2.12, XR2.56
/L_MN: XL2.24, XR2.57
/L_MO: XL2.25, XR2.58
/L_MP: XL2.26, XR2.59
/L_MQ: JQ1.13, JQ2.13, XR2.60
/L_MR: JR1.13, JR2.13, XR2.61
/L_MS: JS1.13, JS2.13, XR2.62
/L_NQ: JQ1.14, JQ2.14, XL2.27
/L_NR: JR1.14, JR2.14, XL2.28
/L_NS: JS1.14, JS2.14, XL2.29
/L_NT: XL2.30, XR2.63
/L_NU: XL2.31, XR2.64
/L_NV: XL2.32, XR3.1
/L_NW: XL2.33, XR3.2
/L_NX: XL2.34, XR3.3
/L_NY: XL2.35, XR3.4
/L_NZ: XL2.36, XR3.5
/L_OQ: JQ1.15, JQ2.15, XL2.37
/L_OR: JR1.15, JR2.15, XL2.38
/L_OS: JS1.15, JS2.15, XL2.39
/L_OT: XL2.40, XR3.6
/L_OU: XL2.41, XR3.7
/L_OV: XL2.42, XR3.8
/L_OW: XL2.43, XR3.9
/L_OX: XL2.44, XR3.10
/L_OY: XL2.45, XR3.11
/L_OZ: XL2.46, XR3.12
/L_PQ: JQ1.16, JQ2.16, XL2.47
/L_PR: JR1.16, JR2.16, XL2.48
/L_PS: JS1.16, JS2.16, XL2.49
/L_PT: XL2.50, XR3.13
/L_PU: XL2.51, XR3.14
/L_PV: XL2.52, XR3.15
/L_PW: XL2.53, XR3.16
/L_PX: XL2.54, XR3.17
/L_PY: XL2.55, XR3.18
/L_PZ: XL2.56, XR3.19
/L_QR: JQ1.18, JQ2.18, JR1.17, JR2.17
/L_QS: JQ1.19, JQ2.19, JS1.17, JS2.17
/L_QT: JQ1.20, JQ2.20, XR3.20
/L_QU: JQ1.21, JQ2.21, XR3.21
/L_QV: JQ1.22, JQ2.22, XR3.22
/L_QW: JQ1.23, JQ2.23, XR3.23
/L_QX: JQ1.24, JQ2.24, XR3.24
/L_QY: JQ1.25, JQ2.25, XR3.25
/L_QZ: JQ1.26, JQ2.26, XR3.26
/L_RS: JR1.19, JR2.19, JS1.18, JS2.18
/L_RT: JR1.20, JR2.20, XR3.27
/L_RU: JR1.21, JR2.21, XR3.28
/L_RV: JR1.22, JR2.22, XR3.29
/L_RW: JR1.23, JR2.23, XR3.30
/L_RX: JR1.24, JR2.24, XR3.31
/L_RY: JR1.25, JR2.25, XR3.32
/L_RZ: JR1.26, JR2.26, XR3.33
/L_ST: JS1.20, JS2.20, XR3.34
/L_SU: JS1.21, JS2.21, XR3.35
/L_SV: JS1.22, JS2.22, XR3.36
/L_SW: JS1.23, JS2.23, XR3.37
/L_SX: JS1.24, JS2.24, XR3.38
/L_SY: JS1.25, JS2.25, XR3.39
/L_SZ: JS1.26, JS2.26, XR3.40
/S_D: JD1.4, JD2.4
/S_E: JE1.5, JE2.5
/S_F: JF1.6, JF2.6
/S_Q: JQ1.17, JQ2.17
/S_R: JR1.18, JR2.18
/S_S: JS1.19, JS2.19

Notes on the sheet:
Diagonal board D2 of 5 - letters D Q E R F S (6 letters, 12 jacks). Link net L_XY joins wire Y of letter X and wire X of letter Y on all four jacks of the two letters; S_X = own wire of letter X. Junction headers: 3 per boundary, ribbon pin n <-> pin n; links sorted by (X,Y) take connector (i // 64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

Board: 4 copper layers, 26 parts (6 on the bottom side), 227 nets, no tracks yet.
